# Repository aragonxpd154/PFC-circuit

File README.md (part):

<p align="center">
  <b>Controle de correção de fator de potência (PFC) + conversor PWM em uma placa-filha de 50 × 36 mm.</b><br>
  Engenharia reversa de uma fonte ATX, remodelada como projeto KiCad completo  esquemático, PCB roteada,<br>
  modelo 3D com componentes reais, arquivos de fábrica, simulações SPICE e uma bancada de testes dedicada.
</p>

---

## Sumário

- [Visão geral](#visão-geral)
- [Números do projeto](#números-do-projeto)
- [Arquitetura](#arquitetura)
- [Teoria de operação](#teoria-de-operação)
- [Interface PSH-BUS (J1)](#interface-psh-bus-j1)
- [As placas](#as-placas)
- [Lista de materiais](#lista-de-materiais)
- [Guia passo a passo](#guia-passo-a-passo)
- [Estrutura do repositório](#estrutura-do-repositório)
- [Limitações e pontos a confirmar](#limitações-e-pontos-a-confirmar)
- [Referências](#referências) · [Licença](#licença)

---

## Visão geral

Fontes de PC com PFC ativo costumam concentrar todo o controle em uma pequena placa vertical encaixada na placa de
potência. Este repositório parte da **PSH CARD1 REV 0.5**  uma dessas placas, levantada por engenharia reversa a partir
da peça física  e a transforma em um projeto de hardware aberto, reprodutível e documentado.

| Original (REV 0.5) | Remodelado (REV 1.0) |
|:---:|:---:|
|  |  |
| Placa-filha retirada da fonte, com o CM6800G (DIP-16) removido do soquete | Modelo 3D gerado do KiCad com os modelos STEP reais dos componentes |
|  |  |
| Esquemático levantado (REV 0.5) | PCB de 2 camadas roteada, renderizada a partir dos Gerbers |

**O que há aqui:**

| | Conteúdo | Onde |
|---|---|---|
| ⚡ | Esquemático KiCad organizado em blocos funcionais, com netlist verificado automaticamente contra a fonte de verdade | [`hardware/psh-card1`](hardware/psh-card1) |
| 🟩 | PCB 50 × 36 mm, 2 camadas, roteada, planos de GND nas duas faces, **DRC 0** | [`psh-card1.kicad_pcb`](hardware/psh-card1/psh-card1.kicad_pcb) |
| 🧪 | **PSH-JIG1**  placa de bancada para energizar e testar a PSH-CARD1 em 12–15 V, sem rede elétrica | [`hardware/psh-jig1`](hardware/psh-jig1) |
| 🏭 | Gerbers X2, furação, BOM, pick-and-place, STEP, PDFs de esquemático e montagem | [`hardware/*/fab`](hardware/psh-card1/fab) |
| 🧊 | Modelos 3D (STEP/GLB/STL) e visualizador interativo three.js | [`docs/3d`](docs/3d) |
| 📈 | Cinco simulações ngspice dos sub-circuitos reais da placa, com gráficos | [`simulation`](simulation) |
| 🧮 | Calculadora de projeto: todos os pontos de operação a partir dos valores da placa | [`tools/pfc_calc.py`](tools/pfc_calc.py) |
| 🔁 | Pipeline 100 % reprodutível: um único arquivo Python descreve o circuito; o resto é gerado | [`tools/eda/designs.py`](tools/eda/designs.py) |

---

## Números do projeto

Valores calculados por [`pfc_calc.py`](tools/pfc_calc.py) e confirmados nas [simulações](simulation/RESULTS.md):

| Parâmetro | Valor | Origem |
|---|---|---|
| Frequência de chaveamento (PFC = PWM) | **83,9 kHz** (simulado: 82,6 kHz) | R26 = 21k5, C20 = 1 nF |
| Barramento PFC regulado | **380 V** (VFB = 2,50 V) | R47 = 5k1 + 770 kΩ na placa-mãe |
| Proteção de sobretensão do PFC | **418 V** (VFB = 2,75 V) | comparador interno |
| Liberação do PWM (VIN-OK) | **372 V** (VFB = 2,45 V) | comparador interno |
| VRMS @ 90 Vac / 230 Vac | **1,00 V / 2,56 V** | divisor 1053k : 13k |
| IAC de pico @ 264 Vac | **397 µA** | R32 + R23 = 940 kΩ |
| Soft-start do PWM | **1,15 s** até 0,7 V | 20 µA em C14 = 33 µF |
| Limite de corrente do PWM | **1,0 V** em DC ILIMIT (2,1 A com shunt de 0,47 Ω) | ciclo a ciclo |
| Compensação de rampa | **+114 mV** no pico (simulado: +109 mV) | Q4 · R35 · C15 · R40 |
| Gate  subida / descida (Ciss 2,2 nF) | **184 ns / 56 ns** | 30 Ω ∥ LL4148 |

---

## Arquitetura

```mermaid
flowchart LR
  subgraph MB["Placa de potência  fonte ATX"]
    direction TB
    AC["Ponte retificadora<br/>VAC_RECT"]
    BOOST["Boost PFC<br/>MOSFET + shunt"]
    BUS["Barramento 380 V<br/>divisor → VFB"]
    FWD["Conversor forward<br/>MOSFET + shunt"]
    OPTO["Optoacoplador<br/>(erro do secundário)"]
    SB["Standby<br/>VCC 12–15 V"]
  end

  subgraph CARD["PSH-CARD1"]
    direction TB
    FF["Feed-forward<br/>IAC · VRMS"]
    CL["Malha de corrente<br/>ISENSE · IEAO"]
    VL["Malha de tensão<br/>VFB · VEAO"]
    U4(("CM6800G"))
    OSC["Oscilador<br/>84 kHz"]
    PWM["VDC · soft-start<br/>ILIMIT + rampa"]
    DRV["Drivers de gate"]
  end

  AC -- "J1.4" --> FF --> U4
  BOOST -- "J1.1 PFC_CS" --> CL --> U4
  BUS -- "J1.6 VFB" --> VL --> U4
  OPTO -- "J1.2 VDC" --> PWM
  FWD -- "J1.8 PWM_CS" --> PWM --> U4
  OSC --> U4
  SB -- "J1.5 VCC" --> U4
  U4 --> DRV
  DRV -- "J1.7 PFC_GATE" --> BOOST
  DRV -- "J1.10 PWM_GATE" --> FWD
```

O **CM6800G** (Champion, pino a pino compatível com ML4800/FAN4800) reúne dois controladores sincronizados no mesmo
oscilador: um **PFC boost de corrente média com modulação na borda de subida** e um **PWM com modulação na borda de
descida**. Essa defasagem entre as bordas reduz a ondulação de corrente no capacitor do barramento  o PWM tende a
drenar energia enquanto o PFC a entrega.

<p align="center"><sub>Esquemático completo em blocos funcionais  <a href="docs/images/psh-card1-schematic.svg">SVG vetorial</a> · <a href="hardware/psh-card1/fab/psh-card1-schematic.pdf">PDF</a></sub></p>

---

## Teoria de operação

<details open>
<summary><b>1 · Oscilador (RAMP1)</b></summary>

RT = R26 (21k5, de VREF) e CT = C20 (1 nF, C0G) definem a rampa entre 1,25 V e 3,75 V; o tempo morto é a descarga de CT
por uma fonte interna:

$$t_{RAMP} = R_T C_T \ln\frac{V_{REF}-1{,}25}{V_{REF}-3{,}75} \approx 0{,}51\,R_T C_T = 10{,}97\ \mu s \qquad t_{DT} = 943\,\Omega \cdot C_T = 0{,}94\ \mu s$$

$$f_{osc} = \frac{1}{t_{RAMP}+t_{DT}} \approx 83{,}9\ \text{kHz}$$

</details>

<details open>
<summary><b>2 · Feed-forward de linha (IAC e VRMS)</b></summary>

A linha retificada (`VAC_RECT`, J1.4) alimenta dois ramos:

- **IAC**  R32 + R23 = 940 kΩ convertem a forma de onda da linha em corrente (135 µA de pico @ 90 Vac): é o *formato* da
  corrente que o PFC vai copiar.
- **VRMS**  R19 + R22 (940 kΩ) → R31 (100 kΩ) → R45 (13 kΩ), com dois polos de filtro (C10 e C17, ≈ 3,4 Hz e 6,3 Hz):
  entrega o valor médio da linha, $V_{RMS} \approx 0{,}9\,V_{ac}\cdot\frac{13k}{1053k}$  **1,00 V em 90 Vac**.

O modulador de ganho divide por $V_{RMS}^2$: a potência de entrada fica praticamente independente da tensão de linha,
e a malha de tensão não precisa "corrigir" mudanças de rede. Os quatro resistores de 470 kΩ estão em 1206 (200 V) e
receberam classe de rede **HV** com 0,6 mm de isolação no roteamento.

</details>

<details open>
<summary><b>3 · Malhas de controle do PFC</b></summary>

| Malha | Pino | Rede | Singularidades |
|---|---|---|---|
| Corrente (interna, rápida) | IEAO (1) | C5 ∥ (R27 + C6), referenciada a VREF | zero 1,59 kHz · polo 35,5 kHz |
| Tensão (externa, lenta) | VEAO (16) | C23 ∥ (R44 + C22) | zero 3,7 Hz · polo 40,7 Hz |

A malha de tensão é deliberadamente lenta (cruzamento abaixo da metade da frequência de linha) para não distorcer a
corrente de entrada a 100/120 Hz. Referenciar a rede da IEAO a VREF em vez de GND é equivalente em AC  VREF é uma
fonte de baixa impedância, desacoplada por C7. O sensor de corrente (ISENSE) recebe a tensão **negativa** do shunt via
filtro R18/C13 (≈ 1,6 MHz); D1 + D3 grampeiam excursões abaixo de ≈ −1,3 V.

</details>

<details open>
<summary><b>4 · Seção PWM  realimentação, soft-start e limite de corrente</b></summary>

- **VDC (pino 6)**  R25 (10k, de VREF) e R46 (15k) fixam **4,5 V** com o optoacoplador cortado; o transistor do opto
  (J1.2) puxa VDC para baixo e reduz a razão cíclica. R43 + C18 e C19 dão a resposta em frequência.
- **Soft-start (pino 5)**  20 µA carregam C14 (33 µF): o PWM começa em ≈ 0,7 V, **1,15 s** depois de o barramento passar
  por 2,45 V em VFB (VIN-OK). O conversor DC-DC só parte com o PFC já regulado.
- **DC ILIMIT (pino 9)**  limite ciclo a ciclo em 1,0 V, com filtro/blanking R29 + C21.

**Compensação de rampa (slope compensation).** Em modo corrente com razão cíclica alta, o laço é instável sem uma rampa
somada ao sinal do sensor (oscilação subharmônica). A placa resolve isso com quatro componentes discretos:

1. Durante o *t<sub>on</sub>* (PWM_OUT alto), D2 bloqueia e R35 carrega C15 a partir de VCC;
2. no *t<sub>off</sub>*, D2 + R36 descarregam C15 até o piso $V_f + (V_{CC}-V_f)\frac{R_{36}}{R_{35}+R_{36}} \approx 1{,}2$ V;
3. Q4 (MMBT3904, seguidor de emissor) copia a rampa sem carregar C15;
4. R40 (22k) soma a rampa ao nó ILIMIT, onde já chega o sinal do shunt por R29 (1k).

</details>

<details open>
<summary><b>5 · Drivers de gate</b></summary>

Cada saída usa a topologia clássica **resistor de turn-on + diodo de turn-off**: o gate carrega lentamente por 30 Ω
(menos EMI e menos *ringing* com a indutância do encapsulamento) e descarrega rápido pelo LL4148 em paralelo (menor
perda de comutação no desligamento). D4 grampeia o *undershoot* negativo em PFC_OUT.

</details>

<details>
<summary><b>6 · Proteções do CM6800 usadas na placa</b></summary>

| Proteção | Limiar | Efeito |
|---|---|---|
| OVP do PFC | VFB > 2,75 V (418 V no barramento) | desliga PFC_OUT |
| VIN-OK | VFB < 2,45 V | mantém o soft-start do PWM descarregado |
| Limite de pico do PFC | ISENSE < −1,0 V | encerra o ciclo do PFC |
| Limite ciclo a ciclo do PWM | DC ILIMIT > 1,0 V | encerra o ciclo e descarrega o soft-start |
| OVP de VCC | VCC > 17,9 V | desliga as saídas |
| Limite de razão cíclica | < 50 % | evita saturação do transformador forward |

</details>

---

## Interface PSH-BUS (J1)

Barra de pinos 1 × 10, 2,54 mm, em ângulo reto  a placa fica em pé sobre a placa de potência.

| Pino | Rede | Direção | Descrição |
|:---:|---|:---:|---|
| 1 | `PFC_CS` | ← | Sensor de corrente do PFC (shunt, tensão negativa) |
| 2 | `VDC` | ← | Realimentação do PWM (coletor do optoacoplador) |
| 3 |  | | **Sem conexão**  distância de isolação para o pino 4 |
| 4 | `VAC_RECT` | ← | Linha retificada (IAC/VRMS)  ⚠️ **alta tensão** |
| 5 | `VCC` | ← | Alimentação 12–15 V vinda do standby |
| 6 | `VFB` | ← | Topo do divisor do barramento de 380 V |
| 7 | `PFC_GATE` | → | Gate do MOSFET boost |
| 8 | `PWM_CS` | ← | Sensor de corrente do conversor DC-DC |
| 9 | `GND` | | Terra do primário |
| 10 | `PWM_GATE` | → | Gate / driver do conversor forward |

---

## As placas

### PSH-CARD1  controlador

<table>
<tr>
<td width="50%"></td>
<td width="50%"></td>
</tr>
<tr><td align="center"><sub>Face superior (todos os SMD)</sub></td><td align="center"><sub>Face inferior  identificação e pinagem de J1</sub></td></tr>
<tr>
<td></td>
<td></td>
</tr>
<tr><td align="center"><sub>Modelo 3D (modelos STEP reais)</sub></td><td align="center"><sub>Cobre: F.Cu (vermelho) · B.Cu (azul) · planos de GND</sub></td></tr>
</table>

| Característica | Valor |
|---|---|
| Dimensões | 50 × 36 mm, cantos com raio de 2 mm |
| Camadas | 2 · FR-4 1,6 mm · cobre 1 oz · ENIG |
| Montagem | SMD só na face superior (0805 / 1206 / MiniMELF / SOT-23), CI em soquete torneado DIP-16 |
| Regras | trilha/isolação 0,2 / 0,2 mm · via 0,6 / 0,3 mm · borda 0,4 mm |
| Classes de rede | `Power` 0,5 mm (VCC, GND, gates) · `HV` 0,6 mm de isolação (VAC_RECT, IAC_M, VRMS_M) |
| Roteamento | Freerouting + planos de GND nas duas faces com alívio térmico |
| Verificação | DRC 0 violações · 0 conexões pendentes · netlist = `designs.py` |

**O que mudou do REV 0.5 para o REV 1.0**

| Item | REV 0.5 (original) | REV 1.0 (este repositório) |
|---|---|---|
| RAMP2 (pino 8) | desenhado em aberto | **JP1** (jumper de solda, fechado) liga RAMP2 a ILIMIT  modo corrente, como na aplicação típica do datasheet |
| Pontos de teste | nenhum | **TP1–TP8**: VREF, VCC, GND, RAMP1, SS, VEAO, IEAO, VRMS |
| Resistores de alta tensão |  | 470 kΩ em 1206 (200 V) + classe `HV` no roteamento |
| CI | soldado em soquete | soquete torneado DIP-16 + modelo 3D do CI encaixado |
| Capacitores sem valor legível |  | valores **sugeridos** e justificados (ver abaixo) |

<details>
<summary><b>Valores sugeridos</b>  capacitores sem valor legível no esquemático original</summary>

| Ref. | Valor | Critério |
|---|---|---|
| C5 / C6 | 470 pF / 10 nF | zero da malha de corrente em 1,6 kHz, polo em 35 kHz (< f<sub>sw</sub>/2) |
| C7 | 1 µF | desacoplamento de VREF |
| C8 | 1 nF | filtro de ruído em VFB (polo ≈ 31 kHz com 5k1) |
| C9 / C24 | 100 nF / 1 µF | desacoplamento de VCC junto ao CI |
| C10 / C17 | 470 nF / 2,2 µF | filtro de 2 polos do VRMS (3,4 Hz / 6,3 Hz)  ondulação < 6 mV |
| C13 | 1 nF | filtro de ISENSE (1,6 MHz com 100 Ω) |
| C15 | 1 nF | τ = 22 µs ≫ período → rampa praticamente linear |
| C18 / C19 | 100 nF / 1 nF | rede de VDC (zero em 1,9 kHz) |
| C21 | 470 pF | blanking do ILIMIT (≈ 340 kHz com 1 kΩ) |
| C22 / C23 | 100 nF / 10 nF | zero da malha de tensão em 3,7 Hz, polo em 41 Hz |

Todos esses valores ficam marcados com `Nota = sugerido` no esquemático e na BOM. Se você tiver a placa original,
meça-os e atualize [`designs.py`](tools/eda/designs.py)  o pipeline regenera tudo.
</details>

### PSH-JIG1  bancada de testes

<table>
<tr>
<td width="55%"></td>
<td width="45%"><br><br></td>
</tr>
</table>

A PSH-JIG1 (90 × 60 mm) permite **energizar e validar a placa de controle com 12–15 V de bancada**, sem placa de
potência e sem tensão de rede:

| Bloco | Componentes | Função |
|---|---|---|
| Entrada | J2, D1 (SS34), C1, C2, LED D2 | 12–15 V com proteção contra inversão |
| Emulação do barramento | R2, **RV1**, R3 | ajusta VFB (2,50 V = 380 V regulado; 2,75 V = OVP) |
| Emulação do opto | R4, **RV2** | puxa VDC para baixo → controla a razão cíclica do PWM |
| Injeção de corrente | R5 + J3, R6 + J4 | gerador de funções em PFC_CS / PWM_CS (10 Ω de terminação) |
| Cargas de gate | R9/C3, R10/C4 | 10 Ω + 4,7 nF ≈ MOSFET de potência real |
| Linha (opcional) | J5 | VAC_RECT  **somente fonte DC isolada e limitada** |
| Medição | TP1–TP8 (Keystone) | ganchos para ponta de prova em todos os sinais relevantes |

> [!TIP]
> O visualizador 3D interativo ([`docs/3d/viewer.html`](docs/3d/viewer.html), arquivo único) abre offline em qualquer
> navegador: `make viewer`. Os arquivos [`psh-card1.stl`](docs/3d/psh-card1.stl) e [`psh-jig1.stl`](docs/3d/psh-jig1.stl)
> podem ser girados direto no GitHub.

---

## Lista de materiais

| Placa | Posições | Linhas de compra | Arquivos |
|---|:---:|:---:|---|
| PSH-CARD1 | 57 | 30 | [BOM](hardware/psh-card1/fab/psh-card1-bom.csv) · [por referência](hardware/psh-card1/fab/psh-card1-parts.csv) · [pick-and-place](hardware/psh-card1/fab/psh-card1-pos.csv) |
| PSH-JIG1 | 33 | 18 | [BOM](hardware/psh-jig1/fab/psh-jig1-bom.csv) · [por referência](hardware/psh-jig1/fab/psh-jig1-parts.csv) · [pick-and-place](hardware/psh-jig1/fab/psh-jig1-pos.csv) |

Semicondutores da PSH-CARD1: **CM6800GIP** (U4), **MMBT3904** (Q4), **6 × LL4148** (D1–D4, D38, D39).
O arquivo "por referência" lista a função de cada componente e suas conexões pino a pino.

---

## Guia passo a passo

### 0 · Pré-requisitos

| Ferramenta | Versão | Para quê |
|---|---|---|
| KiCad (+ footprints, símbolos, modelos 3D) | 7.0 ou superior | abrir/editar as placas, `kicad-cli` |
| Python | 3.10+ | calculadora, geradores, simulações |
| ngspice | 36+ | simulações |
| Java | 17+ | Freerouting (só para **re-rotear**) |
| Node.js | 18+ | visualizador 3D (opcional) |

Testado em **Ubuntu 24.04** (KiCad 7.0.11). Em **Zorin OS 17** / Ubuntu 22.04 o repositório padrão traz o KiCad 6 
instale o 7 pelo PPA oficial antes do `make setup` (`sudo add-apt-repository ppa:kicad/kicad-7.0-releases`).
No Windows, use o WSL2, ou o KiCad nativo + o Python que acompanha o KiCad (que já traz o módulo `pcbnew`).

### 1 · Clonar e instalar

```bash
git clone https://github.com/aragonxpd154/PFC-circuit.git
cd PFC-circuit
make setup          # apt (KiCad, ngspice, Java), pip, Freerouting, three.js
make help           # lista todos os alvos
```

### 2 · Verificar o projeto

```bash
make check
```

```text
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
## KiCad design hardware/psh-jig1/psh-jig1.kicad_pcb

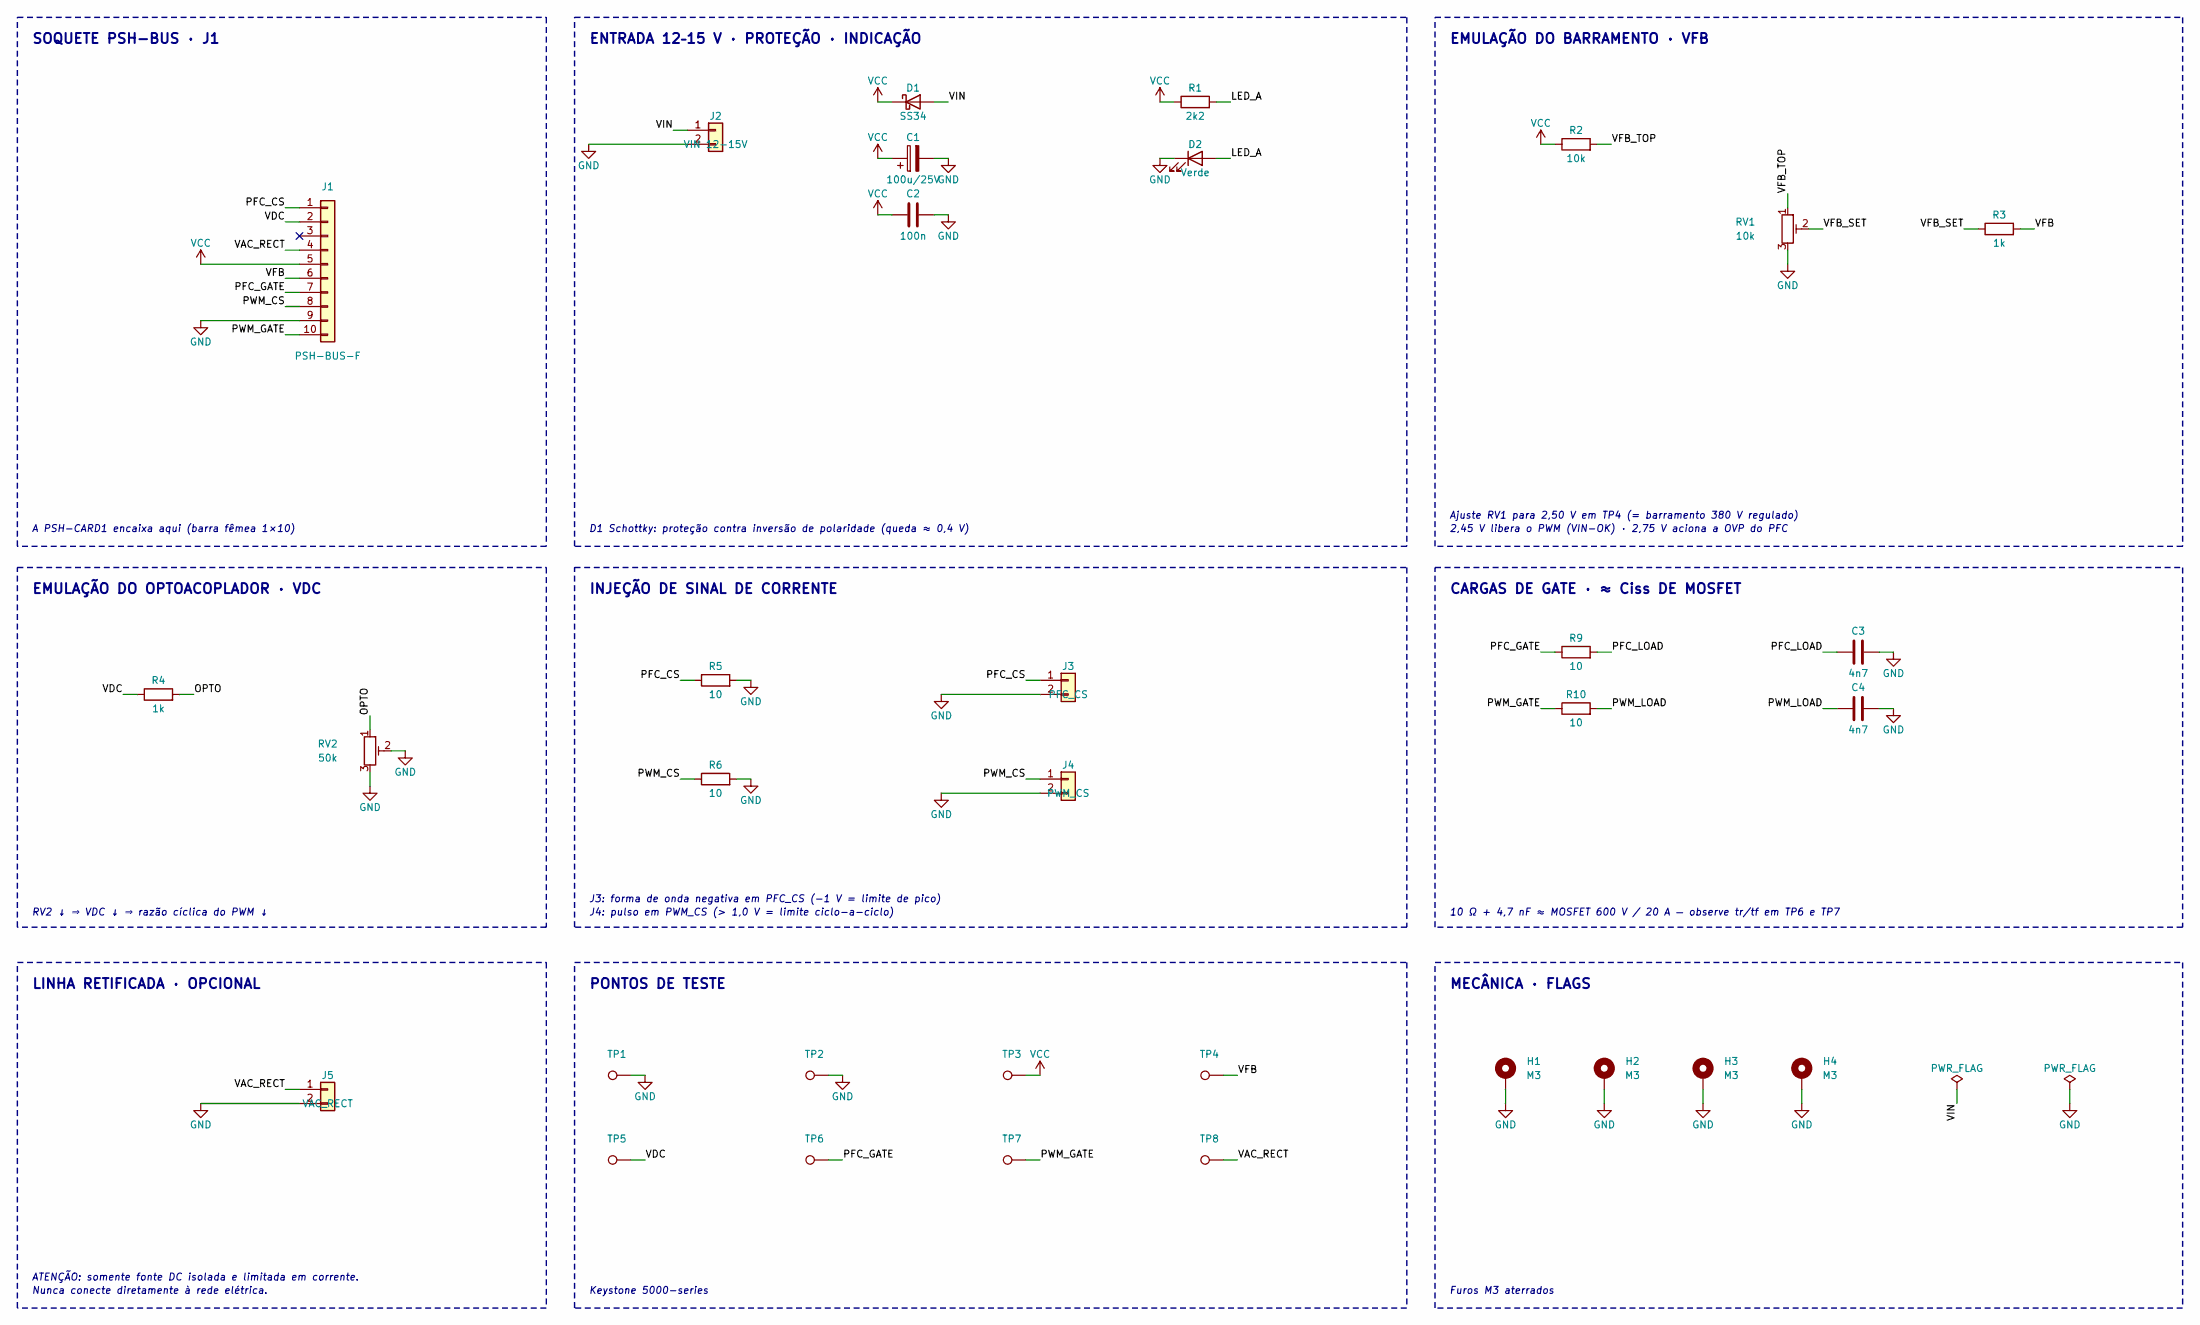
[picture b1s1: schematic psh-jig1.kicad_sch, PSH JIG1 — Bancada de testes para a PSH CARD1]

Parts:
C1: 100u/25V; CP_Elec_6.3x7.7
C2: 100n; C_0805_2012Metric
C3, C4: 4n7; C_1206_3216Metric
D1: SS34; D_SMA; MPN LL4148
D2: Verde; LED_0805_2012Metric
H1, H2, H3, H4: M3; MountingHole_3.2mm_M3_Pad_Via
J1: PSH-BUS-F; PinSocket_1x10_P2.54mm_Vertical
J2: VIN 12-15V; TerminalBlock_Phoenix_MKDS-1,5-2-5.08_1x02_P5.08mm_Horizont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
J3: PFC_CS; PinHeader_1x02_P2.54mm_Vertical
J4: PWM_CS; PinHeader_1x02_P2.54mm_Vertical
J5: VAC_RECT; TerminalBlock_Phoenix_MKDS-1,5-2-5.08_1x02_P5.08mm_Horizont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
R1: 2k2; R_0805_2012Metric
R2: 10k; R_0805_2012Metric
R3, R4: 1k; R_0805_2012Metric
R5, R6, R9, R10: 10; R_0805_2012Metric
RV1: 10k; Potentiometer_Bourns_3296W_Vertical
RV2: 50k; Potentiometer_Bourns_3296W_Vertical
TP1, TP2: GND; TestPoint_Keystone_5000-5004_Miniature
TP3: VCC; TestPoint_Keystone_5000-5004_Miniature
TP4: VFB; TestPoint_Keystone_5000-5004_Miniature
TP5: VDC; TestPoint_Keystone_5000-5004_Miniature
TP6: PFC_GATE; TestPoint_Keystone_5000-5004_Miniature
TP7: PWM_GATE; TestPoint_Keystone_5000-5004_Miniature
TP8: VAC_RECT; TestPoint_Keystone_5000-5004_Miniature

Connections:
GND: C1.2, C2.2, C3.2, C4.2, D2.1 (K), H1.1, H2.1, H3.1, H4.1, J1.9, J2.2, J3.2, J4.2, J5.2, R5.2, R6.2, RV1.3, RV2.2, RV2.3, TP1.1, TP2.1
LED_A: D2.2 (A), R1.2
OPTO: R4.2, RV2.1
PFC_CS: J1.1, J3.1, R5.1
PFC_GATE: J1.7, R9.1, TP6.1
PFC_LOAD: C3.1, R9.2
PWM_CS: J1.8, J4.1, R6.1
PWM_GATE: J1.10, R10.1, TP7.1
PWM_LOAD: C4.1, R10.2
VAC_RECT: J1.4, J5.1, TP8.1
VCC: C1.1, C2.1, D1.1 (K), J1.5, R1.1, R2.1, TP3.1
VDC: J1.2, R4.1, TP5.1
VFB: J1.6, R3.2, TP4.1
VFB_SET: R3.1, RV1.2
VFB_TOP: R2.2, RV1.1
VIN: D1.2 (A), J2.1

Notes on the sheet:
SOQUETE PSH-BUS · J1
A PSH-CARD1 encaixa aqui (barra fêmea 1×10)
ENTRADA 12–15 V · PROTEÇÃO · INDICAÇÃO
D1 Schottky: proteção contra inversão de polaridade (queda ≈ 0,4 V)
EMULAÇÃO DO BARRAMENTO · VFB
Ajuste RV1 para 2,50 V em TP4 (= barramento 380 V regulado)
2,45 V libera o PWM (VIN-OK) · 2,75 V aciona a OVP do PFC
EMULAÇÃO DO OPTOACOPLADOR · VDC
RV2 ↓ ⇒ VDC ↓ ⇒ razão cíclica do PWM ↓
INJEÇÃO DE SINAL DE CORRENTE
J3: forma de onda negativa em PFC_CS (−1 V = limite de pico)
J4: pulso em PWM_CS (> 1,0 V = limite ciclo-a-ciclo)
CARGAS DE GATE · ≈ Ciss DE MOSFET
10 Ω + 4,7 nF ≈ MOSFET 600 V / 20 A — observe tr/tf em TP6 e TP7
LINHA RETIFICADA · OPCIONAL
ATENÇÃO: somente fonte DC isolada e limitada em corrente.
Nunca conecte diretamente à rede elétrica.
PONTOS DE TESTE
Keystone 5000-series
MECÂNICA · FLAGS
Furos M3 aterrados

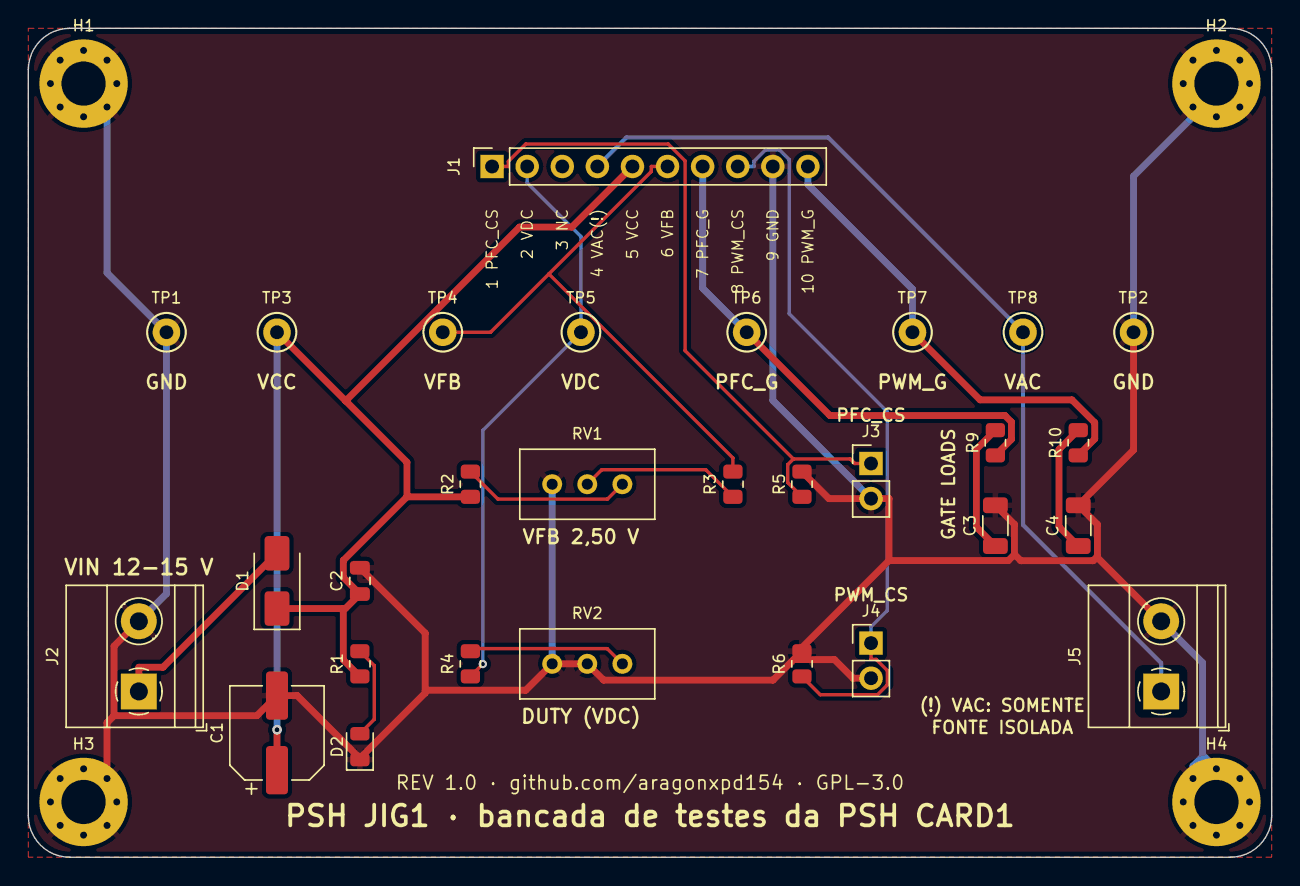
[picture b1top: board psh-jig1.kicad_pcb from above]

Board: 2 copper layers, 90.0 x 60.0 mm, 33 parts (0 on the bottom side), 16 nets.

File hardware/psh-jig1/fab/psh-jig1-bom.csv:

Item,Qtd,Referências,Valor,Footprint,Descrição,MPN,Nota
1,1,D1,SS34,D_SMA,Schottky 3 A 40 V — proteção contra inversão,LL4148,
2,1,D2,Verde,LED_0805_2012Metric,LED indicador de alimentação,,
3,4,R5 R6 R9 R10,10,R_0805_2012Metric,Resistor SMD 0805 1 %,,
4,1,R2,10k,R_0805_2012Metric,Resistor SMD 0805 1 %,,
5,2,R3 R4,1k,R_0805_2012Metric,Resistor SMD 0805 1 %,,
6,1,R1,2k2,R_0805_2012Metric,Resistor SMD 0805 1 %,,
7,1,RV1,10k,Potentiometer_Bourns_3296W_Vertical,"Trimpot multivoltas — ajuste de VFB (2,50 V nominal)",,
8,1,RV2,50k,Potentiometer_Bourns_3296W_Vertical,Trimpot como reostato — emula o transistor do opto,,
9,1,C2,100n,C_0805_2012Metric,Capacitor cerâmico SMD 0805 X7R,,
10,2,C3 C4,4n7,C_1206_3216Metric,Capacitor cerâmico SMD 1206 X7R,,
11,1,C1,100u/25V,CP_Elec_6.3x7.7,Capacitor eletrolítico SMD 6.3x7.7 mm,,
12,1,J3,PFC_CS,PinHeader_1x02_P2.54mm_Vertical,Injeção de sinal em PFC_CS (gerador de funções),,
13,1,J4,PWM_CS,PinHeader_1x02_P2.54mm_Vertical,Injeção de pulso em PWM_CS (teste do limite de 1 V),,
14,1,J5,VAC_RECT,"TerminalBlock_Phoenix_MKDS-1,5-2-5.08_1x02_P5.08mm_Horizontal",Borne VAC_RECT — SOMENTE fonte DC isolada e limitada,,
15,1,J2,VIN 12-15V,"TerminalBlock_Phoenix_MKDS-1,5-2-5.08_1x02_P5.08mm_Horizontal","Borne 2 vias 5,08 mm — alimentação de bancada",,
16,1,J1,PSH-BUS-F,PinSocket_1x10_P2.54mm_Vertical,"Barra fêmea 1×10, 2,54 mm — recebe a PSH-CARD1",,
17,8,TP1 TP2 TP3 TP4 TP5 TP6 TP7 TP8,—,TestPoint_Keystone_5000-5004_Miniature,Ponto de teste Keystone 5000-series (gancho de ponta de prova),,
18,4,H1 H2 H3 H4,—,MountingHole_3.2mm_M3_Pad_Via,Furo de fixação M3 aterrado,,

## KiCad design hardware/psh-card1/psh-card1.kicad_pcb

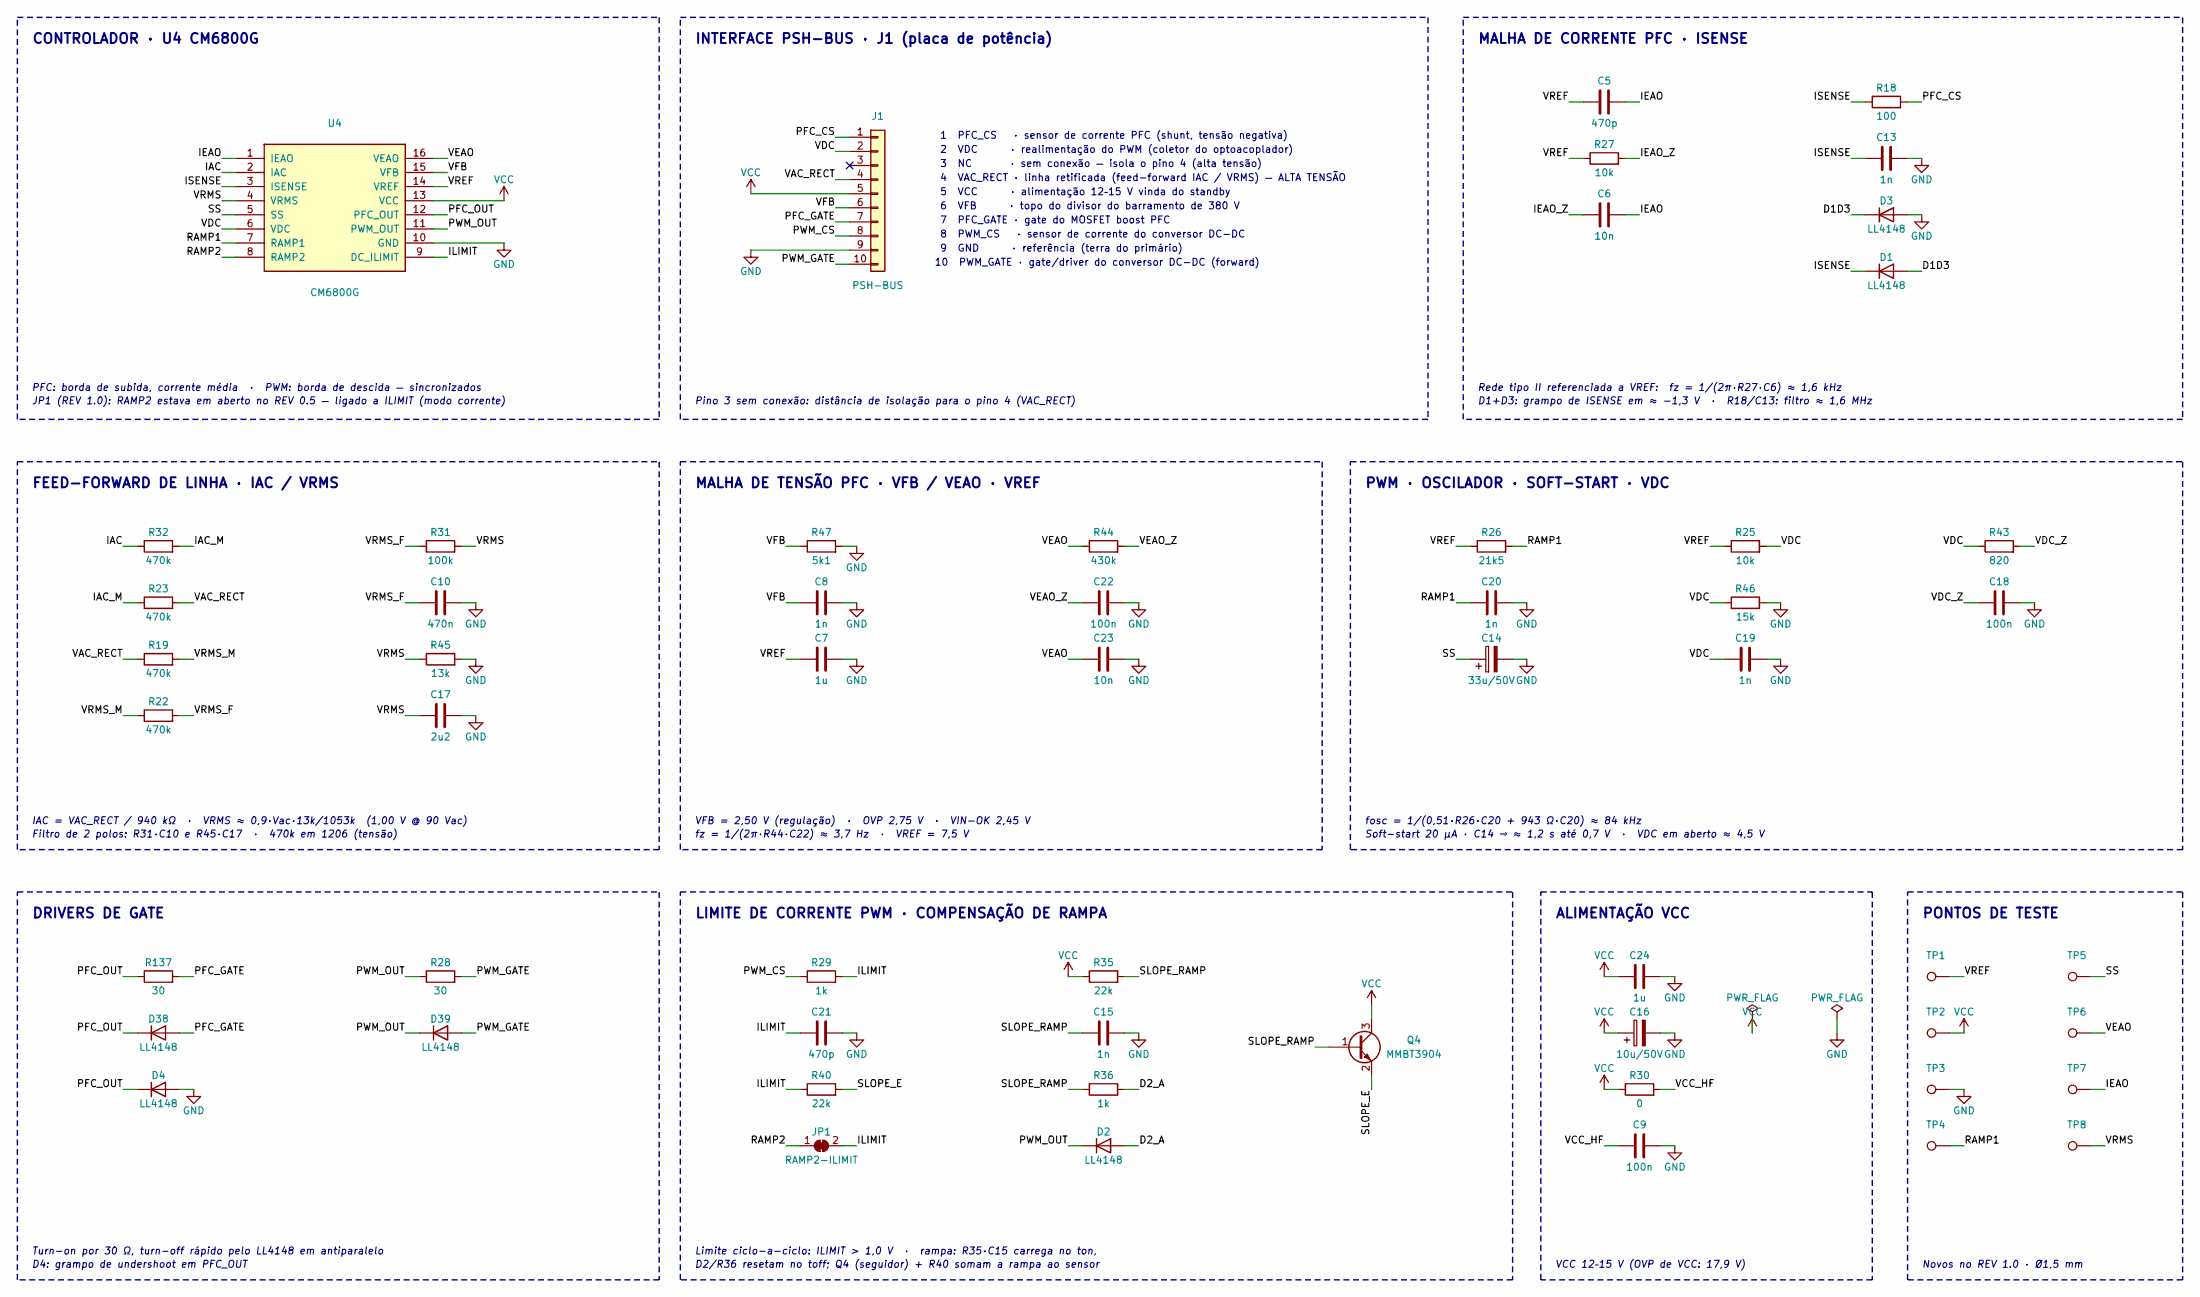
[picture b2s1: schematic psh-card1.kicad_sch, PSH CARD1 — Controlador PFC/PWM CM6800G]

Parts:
C5, C21: 470p; C_0805_2012Metric
C6, C23: 10n; C_0805_2012Metric
C7, C24: 1u; C_0805_2012Metric
C8, C13, C15, C19, C20: 1n; C_0805_2012Metric
C9, C18, C22: 100n; C_0805_2012Metric
C10: 470n; C_0805_2012Metric
C14: 33u/50V; CP_Elec_6.3x5.4
C16: 10u/50V; CP_Elec_5x5.4
C17: 2u2; C_0805_2012Metric
D1, D2, D3, D4, D38, D39: LL4148; D_MiniMELF; MPN LL4148
J1: PSH-BUS; PinHeader_1x10_P2.54mm_Horizontal
JP1: RAMP2-ILIMIT; SolderJumper-2_P1.3mm_Bridged_RoundedPad1.0x1.5mm
Q4: MMBT3904; SOT-23; MPN MMBT3904
R18: 100; R_0805_2012Metric
R19, R22, R23, R32: 470k; R_1206_3216Metric
R25, R27: 10k; R_0805_2012Metric
R26: 21k5; R_0805_2012Metric
R28, R137: 30; R_0805_2012Metric
R29, R36: 1k; R_0805_2012Metric
R30: 0; R_0805_2012Metric
R31: 100k; R_0805_2012Metric
R35, R40: 22k; R_0805_2012Metric
R43: 820; R_0805_2012Metric
R44: 430k; R_0805_2012Metric
R45: 13k; R_0805_2012Metric
R46: 15k; R_0805_2012Metric
R47: 5k1; R_0805_2012Metric
TP1: VREF; TestPoint_Pad_D1.5mm
TP2: VCC; TestPoint_Pad_D1.5mm
TP3: GND; TestPoint_Pad_D1.5mm
TP4: RAMP1; TestPoint_Pad_D1.5mm
TP5: SS; TestPoint_Pad_D1.5mm
TP6: VEAO; TestPoint_Pad_D1.5mm
TP7: IEAO; TestPoint_Pad_D1.5mm
TP8: VRMS; TestPoint_Pad_D1.5mm
U4: CM6800G; DIP-16_W7.62mm_Socket; MPN CM6800GIP

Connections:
D1D3: D1.2 (A), D3.1 (K)
D2_A: D2.2 (A), R36.2
GND: C7.2, C8.2, C9.2, C10.2, C13.2, C14.2, C15.2, C16.2, C17.2, C18.2, C19.2, C20.2, C21.2, C22.2, C23.2, C24.2, D3.2 (A), D4.2 (A), J1.9, R45.2, R46.2, R47.2, TP3.1, U4.10 (GND)
IAC: R32.1, U4.2 (IAC)
IAC_M: R23.1, R32.2
IEAO: C5.2, C6.2, TP7.1, U4.1 (IEAO)
IEAO_Z: C6.1, R27.2
ILIMIT: C21.1, JP1.2 (B), R29.2, R40.1, U4.9 (DC_ILIMIT)
ISENSE: C13.1, D1.1 (K), R18.1, U4.3 (ISENSE)
PFC_CS: J1.1, R18.2
PFC_GATE: D38.2 (A), J1.7, R137.2
PFC_OUT: D4.1 (K), D38.1 (K), R137.1, U4.12 (PFC_OUT)
PWM_CS: J1.8, R29.1
PWM_GATE: D39.2 (A), J1.10, R28.2
PWM_OUT: D2.1 (K), D39.1 (K), R28.1, U4.11 (PWM_OUT)
RAMP1: C20.1, R26.2, TP4.1, U4.7 (RAMP1)
RAMP2: JP1.1 (A), U4.8 (RAMP2)
SLOPE_E: Q4.2 (E), R40.2
SLOPE_RAMP: C15.1, Q4.1 (B), R35.2, R36.1
SS: C14.1, TP5.1, U4.5 (SS)
VAC_RECT: J1.4, R19.1, R23.2
VCC: C16.1, C24.1, J1.5, Q4.3 (C), R30.1, R35.1, TP2.1, U4.13 (VCC)
VCC_HF: C9.1, R30.2
VDC: C19.1, J1.2, R25.2, R43.1, R46.1, U4.6 (VDC)
VDC_Z: C18.1, R43.2
VEAO: C23.1, R44.1, TP6.1, U4.16 (VEAO)
VEAO_Z: C22.1, R44.2
VFB: C8.1, J1.6, R47.1, U4.15 (VFB)
VREF: C5.1, C7.1, R25.1, R26.1, R27.1, TP1.1, U4.14 (VREF)
VRMS: C17.1, R31.2, R45.1, TP8.1, U4.4 (VRMS)
VRMS_F: C10.1, R22.2, R31.1
VRMS_M: R19.2, R22.1

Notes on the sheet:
CONTROLADOR · U4 CM6800G
PFC: borda de subida, corrente média · PWM: borda de descida — sincronizados
JP1 (REV 1.0): RAMP2 estava em aberto no REV 0.5 — ligado a ILIMIT (modo corrente)
INTERFACE PSH-BUS · J1 (placa de potência)
Pino 3 sem conexão: distância de isolação para o pino 4 (VAC_RECT)
1 PFC_CS · sensor de corrente PFC (shunt, tensão negativa)
2 VDC · realimentação do PWM (coletor do optoacoplador)
3 NC · sem conexão — isola o pino 4 (alta tensão)
4 VAC_RECT · linha retificada (feed-forward IAC / VRMS) — ALTA TENSÃO
5 VCC · alimentação 12–15 V vinda do standby
6 VFB · topo do divisor do barramento de 380 V
7 PFC_GATE · gate do MOSFET boost PFC
8 PWM_CS · sensor de corrente do conversor DC-DC
9 GND · referência (terra do primário)
10 PWM_GATE · gate/driver do conversor DC-DC (forward)
MALHA DE CORRENTE PFC · ISENSE
Rede tipo II referenciada a VREF: fz = 1/(2π·R27·C6) ≈ 1,6 kHz
D1+D3: grampo de ISENSE em ≈ −1,3 V · R18/C13: filtro ≈ 1,6 MHz
FEED-FORWARD DE LINHA · IAC / VRMS
IAC = VAC_RECT / 940 kΩ · VRMS ≈ 0,9·Vac·13k/1053k (1,00 V @ 90 Vac)
Filtro de 2 polos: R31·C10 e R45·C17 · 470k em 1206 (tensão)
MALHA DE TENSÃO PFC · VFB / VEAO · VREF
VFB = 2,50 V (regulação) · OVP 2,75 V · VIN-OK 2,45 V
fz = 1/(2π·R44·C22) ≈ 3,7 Hz · VREF = 7,5 V
PWM · OSCILADOR · SOFT-START · VDC
fosc = 1/(0,51·R26·C20 + 943 Ω·C20) ≈ 84 kHz
Soft-start 20 µA · C14 ⇒ ≈ 1,2 s até 0,7 V · VDC em aberto ≈ 4,5 V
DRIVERS DE GATE
Turn-on por 30 Ω, turn-off rápido pelo LL4148 em antiparalelo
D4: grampo de undershoot em PFC_OUT
LIMITE DE CORRENTE PWM · COMPENSAÇÃO DE RAMPA
Limite ciclo-a-ciclo: ILIMIT > 1,0 V · rampa: R35·C15 carrega no ton,
D2/R36 resetam no toff; Q4 (seguidor) + R40 somam a rampa ao sensor
ALIMENTAÇÃO VCC
VCC 12–15 V (OVP de VCC: 17,9 V)
PONTOS DE TESTE
Novos no REV 1.0 · Ø1,5 mm

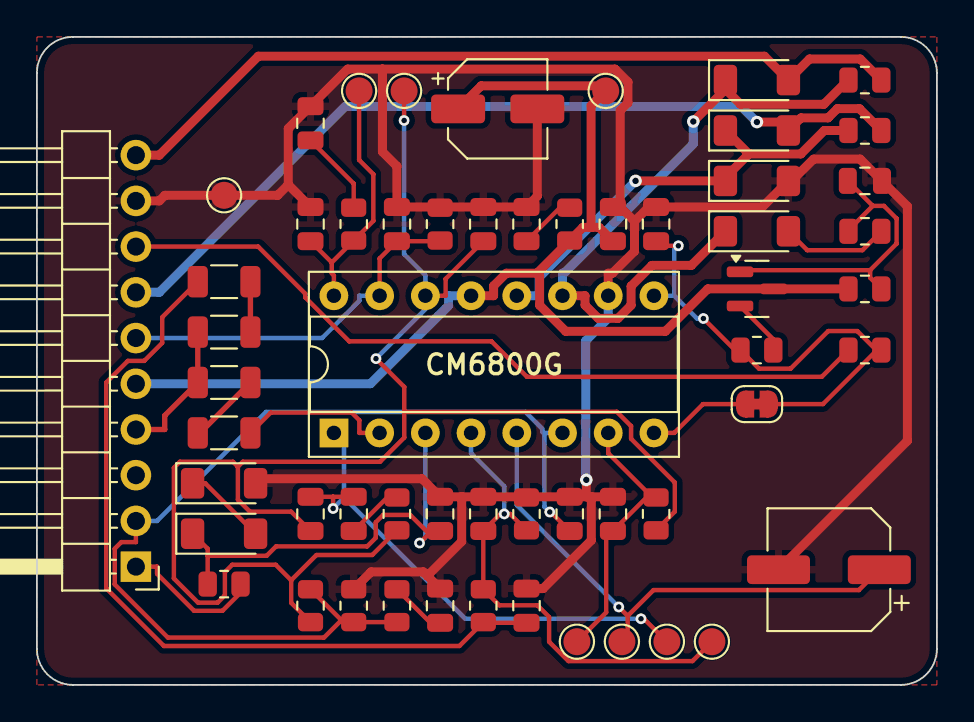
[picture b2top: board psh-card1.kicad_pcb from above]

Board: 2 copper layers, 50.0 x 36.0 mm, 57 parts (0 on the bottom side), 32 nets.

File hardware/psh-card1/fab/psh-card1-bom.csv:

Item,Qtd,Referências,Valor,Footprint,Descrição,MPN,Nota
1,1,U4,CM6800G,DIP-16_W7.62mm_Socket,"Controlador combo PFC/PWM, PDIP-16 (soquete torneado)",CM6800GIP,
2,1,Q4,MMBT3904,SOT-23,NPN seguidor de emissor (buffer da rampa),MMBT3904,
3,6,D1 D2 D3 D4 D38 D39,LL4148,D_MiniMELF,Diodo de sinal rápido 100 V / 200 mA (MiniMELF),LL4148,
4,1,R30,0,R_0805_2012Metric,Resistor SMD 0805 1 %,,
5,1,R18,100,R_0805_2012Metric,Resistor SMD 0805 1 %,,
6,1,R31,100k,R_0805_2012Metric,Resistor SMD 0805 1 %,,
7,2,R25 R27,10k,R_0805_2012Metric,Resistor SMD 0805 1 %,,
8,1,R45,13k,R_0805_2012Metric,Resistor SMD 0805 1 %,,
9,1,R46,15k,R_0805_2012Metric,Resistor SMD 0805 1 %,,
10,2,R29 R36,1k,R_0805_2012Metric,Resistor SMD 0805 1 %,,
11,1,R26,21k5,R_0805_2012Metric,Resistor SMD 0805 1 %,,
12,2,R35 R40,22k,R_0805_2012Metric,Resistor SMD 0805 1 %,,
13,2,R28 R137,30,R_0805_2012Metric,Resistor SMD 0805 1 %,,
14,1,R44,430k,R_0805_2012Metric,Resistor SMD 0805 1 %,,
15,1,R47,5k1,R_0805_2012Metric,Resistor SMD 0805 1 %,,
16,1,R43,820,R_0805_2012Metric,Resistor SMD 0805 1 %,,
17,4,R19 R22 R23 R32,470k,R_1206_3216Metric,Resistor SMD 1206 1 % 200 V,,
18,3,C9 C18 C22,100n,C_0805_2012Metric,Capacitor cerâmico SMD 0805 X7R,,sugerido
19,2,C6 C23,10n,C_0805_2012Metric,Capacitor cerâmico SMD 0805 X7R,,sugerido
20,4,C8 C13 C15 C19,1n,C_0805_2012Metric,Capacitor cerâmico SMD 0805 X7R,,sugerido
21,1,C20,1n,C_0805_2012Metric,Capacitor cerâmico SMD 0805 C0G,,
22,2,C7 C24,1u,C_0805_2012Metric,Capacitor cerâmico SMD 0805 X7R,,sugerido
23,1,C17,2u2,C_0805_2012Metric,Capacitor cerâmico SMD 0805 X7R,,sugerido
24,1,C10,470n,C_0805_2012Metric,Capacitor cerâmico SMD 0805 X7R,,sugerido
25,2,C5 C21,470p,C_0805_2012Metric,Capacitor cerâmico SMD 0805 C0G,,sugerido
26,1,C16,10u/50V,CP_Elec_5x5.4,Capacitor eletrolítico SMD 5x5.4 mm,,
27,1,C14,33u/50V,CP_Elec_6.3x5.4,Capacitor eletrolítico SMD 6.3x5.4 mm,,
28,1,J1,PSH-BUS,PinHeader_1x10_P2.54mm_Horizontal,"Barra de pinos 1×10, 2,54 mm, 90° (encaixe na placa de potência)",,
29,1,JP1,RAMP2-ILIMIT,SolderJumper-2_P1.3mm_Bridged_RoundedPad1.0x1.5mm,Liga RAMP2 ao sensor (modo corrente). Novo no REV 1.0 — ver README,,REV 1.0
30,8,TP1 TP2 TP3 TP4 TP5 TP6 TP7 TP8,—,TestPoint_Pad_D1.5mm,"Ponto de teste SMD Ø1,5 mm",,REV 1.0

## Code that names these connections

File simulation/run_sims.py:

#!/usr/bin/env python3
"""Roda todas as simulações ngspice da PSH-CARD1 e gera os gráficos + RESULTS.md.

Uso:  python3 simulation/run_sims.py          (a partir da raiz do repositório)
Requer: ngspice ≥ 36, numpy, matplotlib
"""
from __future__ import annotations

import re
import subprocess
from pathlib import Path

import matplotlib

matplotlib.use("Agg")
import matplotlib.pyplot as plt  # noqa: E402
import numpy as np  # noqa: E402

HERE = Path(__file__).resolve().parent
ROOT = HERE.parent
IMG = ROOT / "docs" / "images"
OUT = HERE / "out"

# Paleta categórica validada (ordem fixa) + tinta neutra
S1, S2, S3, S4 = "#2a78d6", "#eb6834", "#1baf7a", "#eda100"
INK, INK2, MUTED, GRID, SURF = "#0b0b0b", "#52514e", "#8a8984", "#e6e5e0", "#fcfcfb"

plt.rcParams.update({
    "figure.facecolor": SURF, "axes.facecolor": SURF, "savefig.facecolor": SURF,
    "axes.edgecolor": GRID, "axes.labelcolor": INK2, "axes.titlecolor": INK,
    "axes.titlesize": 12.5, "axes.titleweight": "semibold", "axes.titlelocation": "left",
    "axes.labelsize": 10, "xtick.color": MUTED, "ytick.color": MUTED,
    "xtick.labelsize": 9, "ytick.labelsize": 9, "axes.grid": True, "grid.color": GRID,
    "grid.linewidth": 0.8, "axes.spines.top": False, "axes.spines.right": False,
    "lines.linewidth": 2.0, "legend.frameon": False, "legend.fontsize": 9.5,
    "font.family": "DejaVu Sans", "axes.formatter.use_locale": False,
})


def spice(cir: str) -> str:
    r = subprocess.run(["ngspice", "-b", cir], cwd=HERE, capture_output=True, text=True)
    return r.stdout + r.stderr


def meas(log: str, name: str) -> list[float]:
    return [float(m) for m in re.findall(rf"^{name}\s*=\s*([-\d.eE+]+)", log, re.M)]


def load(path: Path) -> np.ndarray:
    return np.loadtxt(path)


def comma(x: float, fmt: str) -> str:
    return format(x, fmt).replace(".", ",")


def save(fig, name):
    fig.savefig(IMG / name, dpi=160, bbox_inches="tight")
    plt.close(fig)
    print("✓", name)


def main():
    OUT.mkdir(exist_ok=True)
    IMG.mkdir(parents=True, exist_ok=True)
    res = {}

    # ---------------------------------------------------------------- 01
    log = spice("01_oscilador.cir")
    f = float(re.search(r"fosc = ([-\d.eE+]+)", log).group(1))
    res["f_osc"] = f
    d = load(OUT / "01_oscilador.dat")
    t, v = d[:, 0] * 1e6, d[:, 1]
    m = t > 60
    fig, ax = plt.subplots(figsize=(8.6, 3.2))
    ax.plot(t[m], v[m], color=S1)
    for y, lab in [(3.75, "3,75 V — fim da rampa"), (1.25, "1,25 V — início")]:
        ax.axhline(y, color=MUTED, lw=1, ls=(0, (4, 3)))
        ax.text(t[m][-1], y + 0.08, lab, ha="right", va="bottom", color=INK2, fontsize=8.5)
    ax.set(title=f"Oscilador RAMP1 (R26 = 21k5, C20 = 1 nF) — {comma(f / 1e3, '.1f')} kHz simulado",
           xlabel="tempo [µs]", ylabel="V(RAMP1) [V]", ylim=(0.8, 4.2))
    save(fig, "sim-oscilador.png")

    # ---------------------------------------------------------------- 02
    log = spice("02_vrms.cir")
    vavg, vpp, ipk = meas(log, "vrms_avg"), meas(log, "vrms_pp"), meas(log, "iac_pk")
    vacs = [90, 115, 230, 264]
    res["vrms"] = list(zip(vacs, vavg, vpp, ipk))
    fig, ax = plt.subplots(figsize=(8.6, 3.6))
    for vac, col in zip(vacs, [S1, S2, S3, S4]):
        d = load(OUT / f"02_vrms_{vac}")
        ax.plot(d[:, 0], d[:, 1], color=col, label=f"{vac} Vac")
        ax.text(2.02, d[-1, 1], f"{vac} Vac · {comma(d[-1, 1], '.2f')} V", va="center", fontsize=8.5, color=INK2)
    ax.set(title="Feed-forward de linha — VRMS (divisor 1053k/13k + filtro de 2 polos)",
           xlabel="tempo [s]", ylabel="V(VRMS) [V]", xlim=(0, 2.0), ylim=(0, 3.3))
    ax.legend(loc="upper left", ncols=4)
    save(fig, "sim-vrms.png")

    # ---------------------------------------------------------------- 03
    log = spice("03_rampa.cir")
    res["ramp_pk"], res["ilim_pk"], res["ilim_nc_pk"] = (meas(log, k)[0] for k in ("ramp_pk", "ilim_pk", "ilim_nc_pk"))
    d = load(OUT / "03_rampa.dat")
    t = (d[:, 0] - d[0, 0]) * 1e6
    m = t < 36
    fig, axs = plt.subplots(3, 1, figsize=(8.6, 6.4), sharex=True, gridspec_kw={"hspace": 0.38})
    axs[0].plot(t[m], d[m, 1], color=S1)
    axs[0].set(title="PWM_OUT (84 kHz, D = 40 %)", ylabel="[V]")
    axs[1].plot(t[m], d[m, 3], color=S2)
    axs[1].set(title="Rampa em C15 (R35 carrega no ton, D2/R36 resetam no toff)", ylabel="[V]")
    axs[2].plot(t[m], d[m, 5], color=S1, label="com compensação (Q4 + R40)")
    axs[2].plot(t[m], d[m, 7], color=S3, label="sem compensação")
    axs[2].axhline(1.0, color=MUTED, lw=1, ls=(0, (4, 3)))
    axs[2].text(t[m][-1], 1.02, "limite DC ILIMIT = 1,0 V", ha="right", va="bottom", fontsize=8.5, color=INK2)
    axs[2].set(title="Nó DC ILIMIT (pino 9)", ylabel="[V]", xlabel="tempo [µs]", ylim=(-0.05, 1.42))
    axs[2].legend(loc="upper left", ncols=2)
    save(fig, "sim-rampa.png")

    # ---------------------------------------------------------------- 04
    log = spice("04_gate.cir")
    res["tr"], res["tf"], res["tf_b"] = (meas(log, k)[0] for k in ("tr", "tf", "tf_b"))
    d = load(OUT / "04_gate.dat")
    t = d[:, 0] * 1e6
    fig, axs = plt.subplots(1, 2, figsize=(8.6, 3.3), sharey=True, gridspec_kw={"wspace": 0.08})
    for ax, (a, b), ttl in [(axs[0], (0.9, 1.7), "turn-on (R28 = 30 Ω)"), (axs[1], (4.9, 5.7), "turn-off (D39 em paralelo)")]:
        m = (t > a) & (t < b)
        ax.plot(t[m], d[m, 5], color=S3, label="só resistor")
        ax.plot(t[m], d[m, 3], color=S1, label="resistor ∥ LL4148 (placa)")
        ax.set(title=ttl, xlabel="tempo [µs]")
    axs[0].set_ylabel("V(gate) [V]")
    axs[1].legend(loc="upper right")
    fig.suptitle(f"Driver de gate → Ciss 2,2 nF:  tr = {comma(res['tr'] * 1e9, '.0f')} ns · "
                 f"tf = {comma(res['tf'] * 1e9, '.0f')} ns (vs {comma(res['tf_b'] * 1e9, '.0f')} ns sem diodo)",
                 x=0.125, ha="left", fontsize=12.5, fontweight="semibold", color=INK, y=1.02)
    save(fig, "sim-gate.png")

    # ---------------------------------------------------------------- 05
    spice("05_compensacao.cir")
    d = load(OUT / "05_comp.dat")
    fq = d[:, 0]
    fig, ax = plt.subplots(figsize=(8.6, 3.6))
    ax.loglog(fq, d[:, 1], color=S1, label="IEAO — malha de corrente")
    ax.loglog(fq, d[:, 3], color=S2, label="VEAO — malha de tensão")
    for fz, col, lab in [(1 / (2 * np.pi * 10e3 * 10e-9), S1, "zero 1,6 kHz"), (1 / (2 * np.pi * 430e3 * 100e-9), S2, "zero 3,7 Hz")]:
        ax.axvline(fz, color=col, lw=1, ls=(0, (4, 3)), alpha=0.7)
        ax.text(fz * 1.15, ax.get_ylim()[1] if False else 3e6, lab, color=INK2, fontsize=8.5, va="top")
    ax.set(title="Redes de compensação — |Z| na saída dos amplificadores de transcondutância",
           xlabel="frequência [Hz]", ylabel="|Z| [Ω]", xlim=(0.1, 1e6))
    ax.legend(loc="lower left")
    save(fig, "sim-compensacao.png")

    # ---------------------------------------------------------------- RESULTS.md
    import sys
    sys.path.insert(0, str(ROOT / "tools"))
    import pfc_calc
    c = pfc_calc.compute(pfc_calc.defaults())
    rows = "\n".join(f"| {v} Vac | {comma(a, '.3f')} V ({comma(t['VRMS_V'], '.3f')} V) | {comma(p * 1e3, '.1f')} mV | {comma(i * 1e6, '.0f')} µA ({comma(t['IAC_pk_uA'], '.0f')} µA) |"
                     for (v, a, p, i), t in zip(res["vrms"], c["linha"]["tabela"]))

    md = f"""# Resultados das simulações (gerado por `run_sims.py`)

| Grandeza | Simulado | Calculado (`tools/pfc_calc.py`) |
|---|---|---|
| Frequência do oscilador | {comma(res['f_osc'] / 1e3, '.1f')} kHz | {comma(c['oscilador']['f_osc_Hz'] / 1e3, '.1f')} kHz |
| Pico da rampa em C15 (D = 40 %) | {comma(res['ramp_pk'], '.2f')} V | {comma(c['rampa']['V_rampa_pico_V'], '.2f')} V |
| Rampa somada em ILIMIT (pico) | {comma((res['ilim_pk'] - res['ilim_nc_pk']) * 1e3, '.0f')} mV | {comma(c['rampa']['acrescimo_ILIMIT_V'] * 1e3, '.0f')} mV |
| Gate: tempo de subida 10–90 % | {comma(res['tr'] * 1e9, '.0f')} ns | — |
| Gate: tempo de descida 90–10 % | {comma(res['tf'] * 1e9, '.0f')} ns (sem diodo: {comma(res['tf_b'] * 1e9, '.0f')} ns) | — |

## Feed-forward de linha

| Linha | VRMS médio (calculado) | Ondulação p-p | IAC de pico (calculado) |
|---|---|---|---|
{rows}
"""
    (HERE / "RESULTS.md").write_text(md, encoding="utf-8")
    print("✓ RESULTS.md")


if __name__ == "__main__":
    main()

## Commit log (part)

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2021-11-15 CIRCUIT

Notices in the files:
README.md:
https://img.shields.io/badge/licen%C3%A7a-GPL--3.0-d6ac48
Distribuído sob a **GNU GPL v3.0**  veja [`LICENSE`](LICENSE). Hardware fornecido "como está", sem garantias; o uso
hardware/psh-card1/psh-card1.kicad_pcb:
GPL-3.0 · (!) ALTA TENSÃO EM J1.4
hardware/psh-card1/psh-card1.kicad_sch:
Licença GPL-3.0 · github.com/aragonxpd154/PFC-circuit
hardware/psh-jig1/psh-jig1.kicad_pcb:
REV 1.0 · github.com/aragonxpd154 · GPL-3.0
